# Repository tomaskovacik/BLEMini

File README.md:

atemp to make clone using HM-10S (CC2540) module

BLEMini
=======

BLE Mini is a small, certified BLE development board for makers to do their innovative projects. It can be used for BLE development using TI CC254x SDK.

We also provide some examples to show how to integrate this board to other platform such as Arduino. It can also be run independently.

You can write your own firmware for the BLE Mini, get TI CC254x SDK and IAR 8051 C compiler from their website. The current version for CC254x SDK is v1.4.0 and IAR 8051 C compiler is v8.20.2.

Note:

1. For firmware update, since TI's bootloader (UBL) on the BLE Mini does not work on Windows 8.1 or later, OSX and Linux. It only works fine on Windows 7.

2. The CC254x SDK can only work on Windows platform (using IAR C Compiler). Suggest you using TI's CC Debugger for doing your own firmware.

3. If you are using Windows 8.1 or later, Linux or Mac, highly recommend you to install a copy of Windows 7 using Virtual Box or Parallels Desktop.

Dependency
==========

BLE Mini requires different firmwares to function, so it depends on some opensource projects:<br/>
- [Biscuit Firmware](https://github.com/RedBearLab/Biscuit) (a BLE to UART firmware, factory default)
- [MiniBeacon Firmware](https://github.com/RedBearLab/MiniBeacon)
- [BLE_HCI](https://github.com/RedBearLab/BLE_HCI)

All are hosted at https://github.com/RedBearLab

Please refers to those repositories for source code and details.

Examples
========

Samples show how to connect iOS/Mac to your Arduino via BLE link (with the Biscuit firmware). More interesting resource will be added soon.

SimpleControls
- This demo shows how to create controls for common Arduino pin settings
- Please refer to "Readme_SimpleControls.txt" for details

Chat
- A simple chat demo for iOS to talk to Arduino
- Please refer to "Readme_Chat.txt" for details

MiniBeacon
- Implemented Apple's iBeacon spec.
- Use our MiniBeacon iOS App to set the parameters.

Update Firmawre
===============

Only work on Windows PC, press and hold the button on the board and connect it to an USB port, a MSD drive will be mounted and then drag and drop the firmware file (.bin) to the drive.

Resources
=========

1. TI CC254x SDK<br/>
http://www.ti.com/tool/ble-stack

2. TI CC254x forum<br/>
http://e2e.ti.com/support/low_power_rf/f/538.aspx 

3. TI CC2540 Datasheet
http://www.ti.com/lit/ds/symlink/cc2540.pdf

4. TI CC254x Software Developer's Guide
http://www.ti.com/lit/swru271
 
5. IAR C compiler for 8051 (CC254x is based on 8051)<br/>
http://www.iar.com/Products/IAR-Embedded-Workbench/8051/

6. RBL BLE Mini<br/>
http://redbearlab.com/blemini/

7. RBL BLE Mini Forum - Discussion and sharing<br/>
https://redbearlab.zendesk.com/forums

License
=======

Copyright (c) 2013-2014 RedBearLab

Permission is hereby granted, free of charge, to any person obtaining a copy
of this software and associated documentation files (the "Software"), to deal 
in the Software without restriction, including without limitation the rights 
to use, copy, modify, merge, publish, distribute, sublicense, and/or sell
copies of the Software, and to permit persons to whom the Software is
furnished to do so, subject to the following conditions:

The above copyright notice and this permission notice shall be included in all
copies or substantial portions of the Software.

THE SOFTWARE IS PROVIDED "AS IS", WITHOUT WARRANTY OF ANY KIND, EXPRESS OR
IMPLIED, INCLUDING BUT NOT LIMITED TO THE WARRANTIES OF MERCHANTABILITY,
FITNESS FOR A PARTICULAR PURPOSE AND NONINFRINGEMENT. IN NO EVENT SHALL THE
AUTHORS OR COPYRIGHT HOLDERS BE LIABLE FOR ANY CLAIM, DAMAGES OR OTHER 
LIABILITY, WHETHER IN AN ACTION OF CONTRACT, TORT OR OTHERWISE, ARISING FROM,
OUT OF OR IN CONNECTION WITH THE SOFTWARE OR THE USE OR OTHER DEALINGS IN THE
SOFTWARE.

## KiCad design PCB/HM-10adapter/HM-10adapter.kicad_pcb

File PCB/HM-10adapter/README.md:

attempt to recreate BLEmini using HM-10S module one using CC2540, and so has USB capability

for now, UBL-1.3 works, but I got lot of errors in linux, on windows drive showed up with empty DEFAULT.CFG file. quick copy of firmware works, but after restart of module, firmware file is not there ...

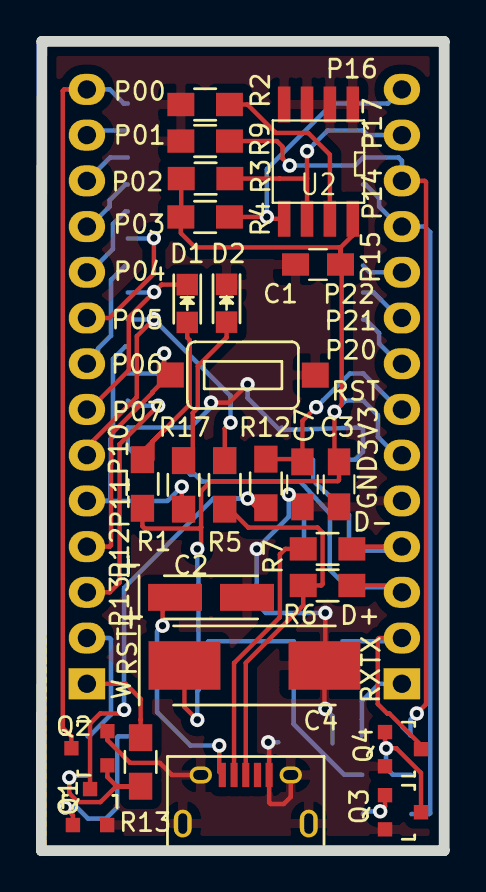
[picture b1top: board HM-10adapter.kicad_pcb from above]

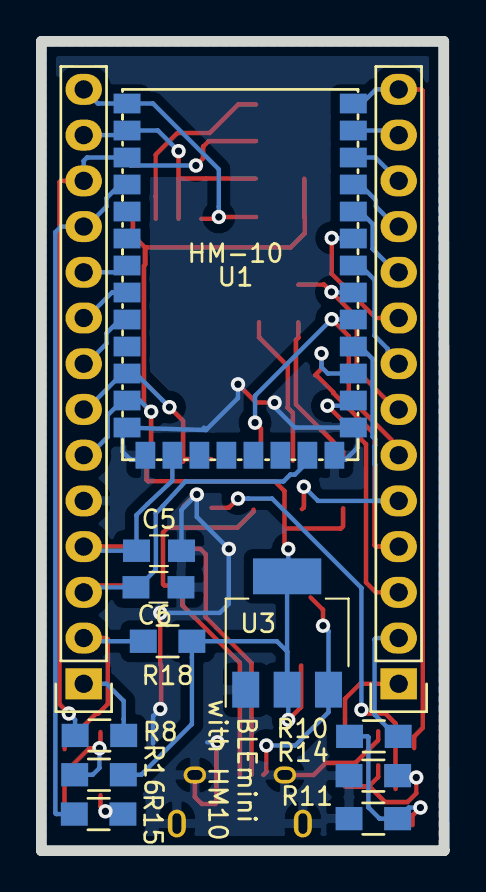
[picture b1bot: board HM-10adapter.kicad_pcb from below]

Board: 2 copper layers, 22.4 x 45.0 mm, 38 parts (13 on the bottom side), 39 nets.

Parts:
C1, C3: 100n; C_0805_HandSoldering
C2: 1u/16V; TantalC_SizeA_EIA-3216_HandSoldering
C4: 10u/16v; TantalC_SizeD_EIA-7343_HandSoldering
C5, C6: 47p; C_0805_HandSoldering
C7: 1n; C_0805_HandSoldering
D1, D2: LED; LED-0805
J1: USB_B_Micro; USB_Micro-B
J2, J3: Conn_01x14; Pin_Header_Straight_1x14
Q1, Q2, Q3, Q4: BSS138; SOT-23
R1, R2, R3, R4, R17: 10K; R_0805_HandSoldering
R5: 1k5; R_0805_HandSoldering
R6, R7: 22; R_0805_HandSoldering
R8, R15: 1k; R_0805_HandSoldering
R9, R12: 2k2; R_0805_HandSoldering
R10, R13: 10k; R_0805_HandSoldering
R11, R14: 100k; R_0805_HandSoldering
R16, R18: 47k; R_0805_HandSoldering
SW1: SPST; 3x6x2.5mm_tact_switch
U1: HM-10
U2: AT24CS01-SSHM; SOIC-8-N_wide_pads
U3: AP1117-33; SOT-223-3_TabPin2

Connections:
/3V3: C1.1, C3.1, C4.1, J2.6, R1.1, R3.1, R4.1, R16.2, R18.2, U1.12, U2.8, U3.2
/D+: C6.1, J2.3, R6.2, U1.20
/D-: C5.1, J2.4, R7.1, U1.15
/GND: C1.2, C2.2, C3.2, C4.2, C5.2, C6.2, C7.2, D2.1, J1.5, J1.6, J2.5, Q1.2, Q2.2, Q3.2, Q4.2, R2.1, R9.1, R11.1, R14.1, SW1.2, U1.13, U1.14, U1.21, U1.22, U2.1, U2.2, U2.3, U2.4, U3.1
/P0_0: J3.14, Q2.3, U1.34
/P0_1: J3.13, U1.33
/P0_2: J3.12, U1.32
/P0_3: J3.11, U1.31
/P0_4: J3.10, U1.30
/P0_5: J3.9, U1.29
/P0_6: J3.8, U1.28
/P0_7: D1.1, J3.7, U1.27
/P1_0: J3.6, R5.1, U1.26
/P1_1: J3.5, R17.1, U1.25
/P1_2: J3.4, SW1.1, U1.24
/P1_3: J3.3, U1.23
/P1_4: J2.12, R8.2, R9.2, U1.3
/P1_5: J2.11, R15.1, U1.4
/P1_6: J2.14, R4.2, U1.1, U2.5
/P1_7: J2.13, R3.2, U1.2, U2.6
/P2_0: J2.8, U1.9
/P2_1: J2.9, U1.8
/P2_2: J2.10, U1.7
/REST: J3.2, R10.1
/RST: C7.1, J2.7, R12.2, U1.11
/RX: J2.1, R8.1
/TX: J2.2, Q4.3, R18.1
/Vin: C2.1, J1.1, U3.3
/WAKEUP: J3.1, R13.1
unnamed: D1.2, R1.2
unnamed: D2.2, R17.2
unnamed: J1.2, R7.2
unnamed: J1.3, R5.2, R6.1
unnamed: Q1.1, R10.2, R11.2
unnamed: Q1.3, R12.1
unnamed: Q2.1, R13.2, R14.2
unnamed: Q3.1, R15.2
unnamed: Q3.3, Q4.1, R16.1
unnamed: R2.2, U2.7

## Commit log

2020-04-16 kicad files using HM-10 module
2020-04-16 readme
2020-04-16 bin generated with hex2bin
2020-04-16 info in readme
